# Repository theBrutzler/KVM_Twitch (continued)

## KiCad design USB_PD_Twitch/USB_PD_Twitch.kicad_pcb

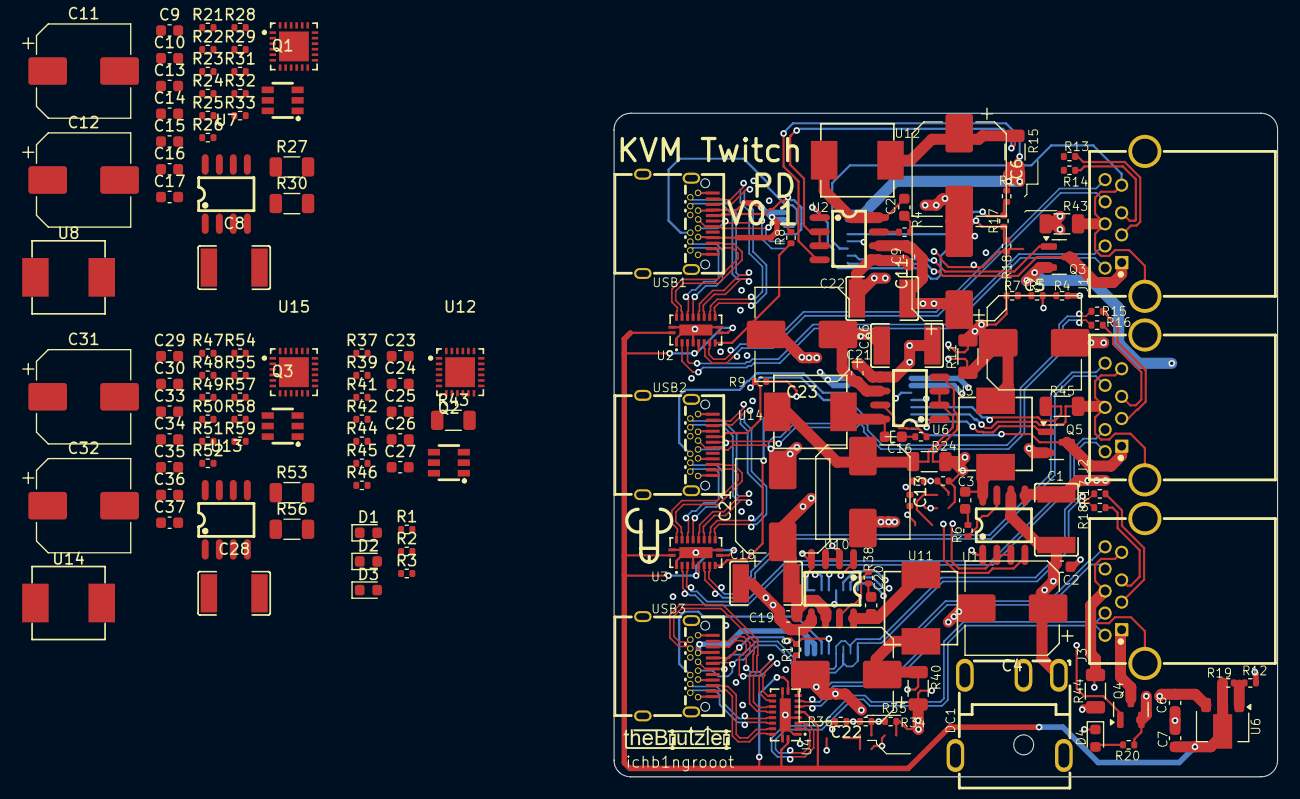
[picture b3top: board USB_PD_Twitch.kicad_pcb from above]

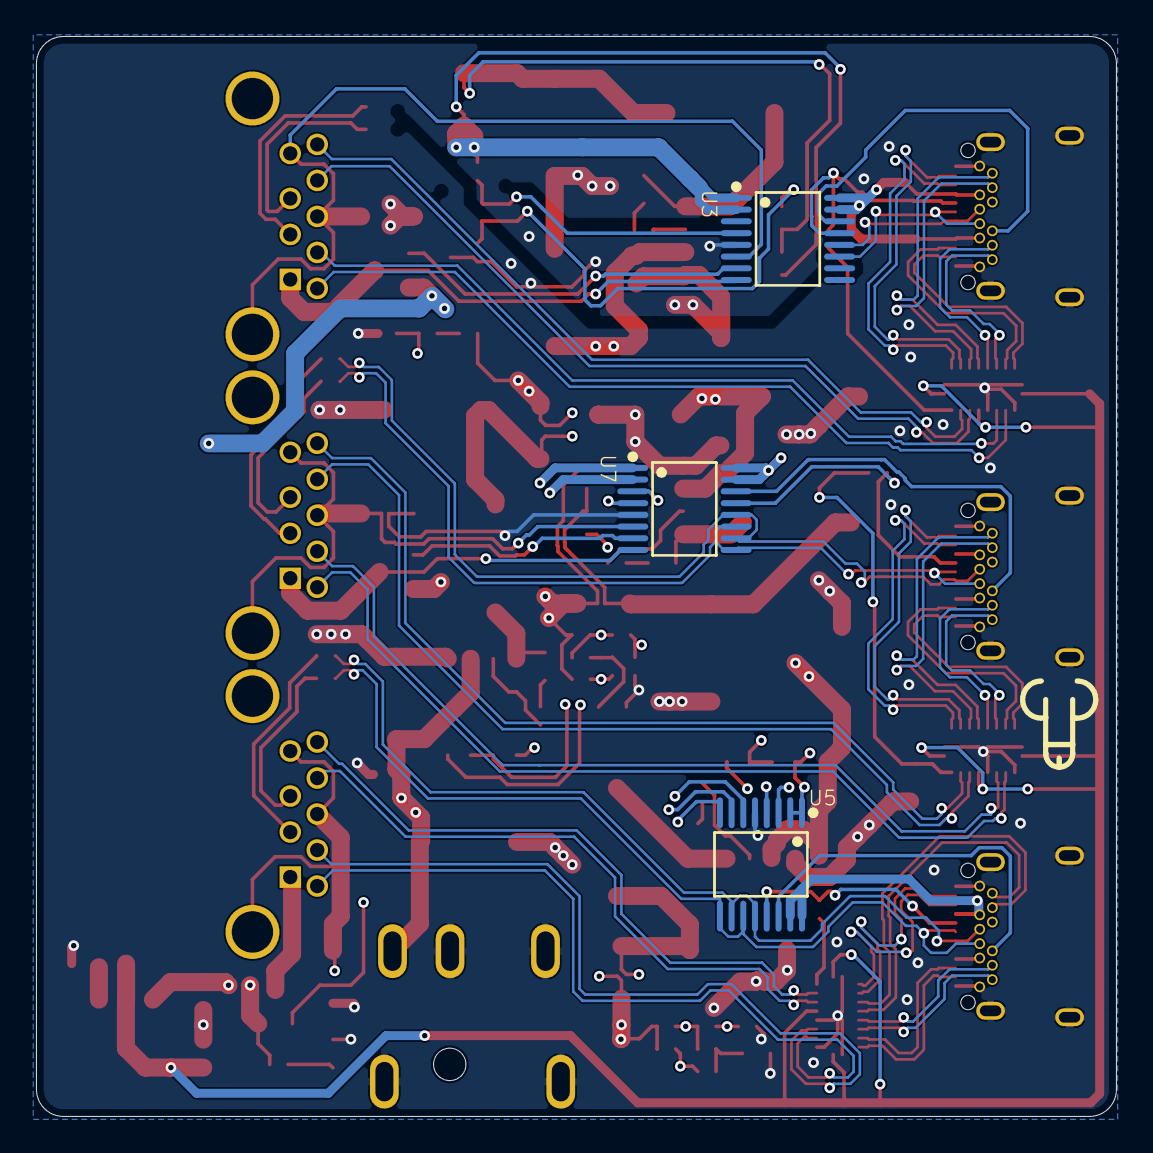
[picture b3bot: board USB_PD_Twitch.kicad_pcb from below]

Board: 4 copper layers, 60.0 x 60.0 mm, 158 parts (3 on the bottom side), 159 nets.

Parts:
C1: 2u2; C1812
C2, C2#2, C3, C9, C9#2, C10, C13#2, C14, C15, C16, C16#2, C17, C19, C20, C21#2, C23, C24, C25, C26#2, C27, C29, C30, C33, C34, C35, C36, C37: 100n; C_0603_1608Metric
C4, C5, C6#2, C11, C11#2, C12, C13, C21, C22#2, C23#2, C31, C32: 100u; CP_Elec_8x10
C6, C7: 10u; C_0603_1608Metric
C8, C18, C22, C26, C28: 22u; C1812
D1, D2, D3, D4: LED; LED_0603_1608Metric
DC1: DC-044A-25; DC-IN-TH_DC-044A-25A
J1, J2, J3: USB3_A; USB-3.0-A-TH_HC-ST-003-01-Z
Q1, Q2, Q3#2: FS8205A_C908265; SOT-23-6_L2.9-W1.6-P0.95-LS2.8-BR
Q3, Q4, Q5: Q_PMOS_GSD; SOT-23
R1, R2, R3, R12, R20, R28, R29, R41, R42, R54, R55: 10K; R_0402_1005Metric
R4, R6, R6#2, R13, R14, R15, R16, R17#2, R18#2, R25, R38, R51: 22R; R_0402_1005Metric
R4#2, R18, R23, R36, R37, R49: 25K; R_0402_1005Metric
R5, R17, R19, R22, R33, R35, R48: 8K; R_0402_1005Metric
R7, R16#2, R21, R31, R32#2, R33#2, R34, R44#2, R46, R47, R57, R59: 100K; R_0402_1005Metric
R8, R9, R10: 0R; R_0402_1005Metric
R11, R15#2, R24, R27, R40, R43#2, R44, R45, R53: 10m; R_1206_3216Metric
R24#2, R37#2, R50: 29K; R_0402_1005Metric
R26, R39, R52: 18K; R_0402_1005Metric
R30, R43, R56: 6m; R_1206_3216Metric
R32, R45#2, R58: 100R; R_0402_1005Metric
U1, U2#2, U6#2, U7, U10, U13: NDP1360KC; SOP-8_L4.9-W3.9-P1.27-LS6.0-BL
U2, U3, U4: CH482D; VFQFN-20_L4.5-W2.5-P0.5-BL-EP
U3#2, U5#2, U7#2: XPD738B20; TSSOP-16_L5.0-W4.4-P0.65-LS6.4-BL
U5, U8, U11, U12, U14, U14#2: CXP0650-220M-AG(22UH); IND-SMD_L7.1-W6.6_CXP0650
U6: LM317L_SOT-89; SOT-89-3
U9, U12#2, U15: TPS25740ARGER; VQFN-24_L4.0-W4.0-P0.50-TL-EP
USB1, USB2, USB3: HX TYPE-C 24P QCHT; TYPE-C-SMD_TYPE-C-24P-QCHT

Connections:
+3V3: C7.1, R1.1, R2.1, R3.1, R19.1, U2.5 (VDD), U2.9 (VDD), U2.20 (VDD), U3.5 (VDD), U3.9 (VDD), U3.20 (VDD), U4.5 (VDD), U4.9 (VDD), U4.20 (VDD), U6.2 (VO)
+5V: C6.1, J1.1 (VBUS), J2.1 (VBUS), J3.1 (VBUS), Q3.2 (S), Q4.2 (S), Q5.2 (S), R7.1, R11.2, R20.1, U1.4 (CSN2), U6.3 (VI)
+24V: C1.2, C2.2, C4.1, C8.2, C9.2, C9#2.2, C11.1, C11#2.1, C18.2, C19.2, C21.1, C21#2.2, C22.2, C23#2.1, C26.2, C28.2, C29.2, C31.1, DC1.4, U1.6 (VIN), U2#2.6 (VIN), U6#2.6 (VIN), U7.6 (VIN), U10.6 (VIN), U13.6 (VIN)
/A1_SSRX+: U2.14 (SSA1X), USB1.B11 (SSRXp1)
/A1_SSRX-: U2.13 (SSA1Y), USB1.B10 (SSRXn1)
/A1_SSTX+: U2.12 (SSB1X), USB1.A2 (SSTXp1)
/A1_SSTX-: U2.11 (SSB1Y), USB1.A3 (SSTXn1)
/A2_SSRX+: U2.18 (SSA0X), USB1.A11 (SSRXp2)
/A2_SSRX-: U2.17 (SSA0Y), USB1.A10 (SSRXn2)
/A2_SSTX+: U2.16 (SSB0X), USB1.B2 (SSTXp2)
/A2_SSTX-: U2.15 (SSB0Y), USB1.B3 (SSTXn2)
/A_CC1: R8.2, U3#2.13 (CC1), U9.2 (CC1), USB1.A5 (CC1)
/A_CC2: U3#2.14 (CC2), U9.3 (CC2), USB1.B5 (CC2)
/A_D+: R14.2, U3#2.11 (DP1), USB1.A6 (DP1), USB1.B6 (DP2)
/A_D-: R13.1, U3#2.12 (DM1), USB1.A7 (DN2), USB1.B7 (DN2)
/A_SSRX+: J1.6 (SSRX+), U2.6 (SSBX)
/A_SSRX-: J1.5 (SSRX-), U2.7 (SSBY)
/A_SSTX+: J1.9 (SSTX+), U2.2 (SSAX)
/A_SSTX-: J1.8 (SSTX-), U2.3 (SSAY)
/A_USB_CC_DET: D3.1 (K), U9.11 (~UFP)
/A_VBUS: R30.2, R32.1, U3#2.15 (VBUS), U3#2.16 (VBUS), U9.21 (VBUS), USB1.A4 (VBUS), USB1.A9 (VBUS), USB1.B4 (VBUS), USB1.B9 (VBUS)
/B1_SSRX+: U3.14 (SSA1X), USB2.B11 (SSRXp1)
/B1_SSRX-: U3.13 (SSA1Y), USB2.B10 (SSRXn1)
/B1_SSTX+: U3.12 (SSB1X), USB2.A2 (SSTXp1)
/B1_SSTX-: U3.11 (SSB1Y), USB2.A3 (SSTXn1)
/B2_SSRX+: U3.18 (SSA0X), USB2.A11 (SSRXp2)
/B2_SSRX-: U3.17 (SSA0Y), USB2.A10 (SSRXn2)
/B2_SSTX+: U3.16 (SSB0X), USB2.B2 (SSTXp2)
/B2_SSTX-: U3.15 (SSB0Y), USB2.B3 (SSTXn2)
/B_CC1: R9.2, U7#2.13 (CC1), U15.2 (CC1), USB2.A5 (CC1)
/B_CC2: U7#2.14 (CC2), U15.3 (CC2), USB2.B5 (CC2)
/B_D+: R16.2, U7#2.11 (DP1), USB2.A6 (DP1), USB2.B6 (DP2)
/B_D-: R15.1, U7#2.12 (DM1), USB2.A7 (DN2), USB2.B7 (DN2)
/B_SSRX+: J2.6 (SSRX+), U3.6 (SSBX)
/B_SSRX-: J2.5 (SSRX-), U3.7 (SSBY)
/B_SSTX+: J2.9 (SSTX+), U3.2 (SSAX)
/B_SSTX-: J2.8 (SSTX-), U3.3 (SSAY)
/B_USB_CC_DET: D1.1 (K), U15.11 (~UFP)
/B_VBUS: R56.2, R58.1, U7#2.15 (VBUS), U7#2.16 (VBUS), U15.21 (VBUS), USB2.A4 (VBUS), USB2.A9 (VBUS), USB2.B4 (VBUS), USB2.B9 (VBUS)
/C1_SSRX+: U4.14 (SSA1X), USB3.B11 (SSRXp1)
/C1_SSRX-: U4.13 (SSA1Y), USB3.B10 (SSRXn1)
/C1_SSTX+: U4.12 (SSB1X), USB3.A2 (SSTXp1)
/C1_SSTX-: U4.11 (SSB1Y), USB3.A3 (SSTXn1)
/C2_SSRX+: U4.18 (SSA0X), USB3.A11 (SSRXp2)
/C2_SSRX-: U4.17 (SSA0Y), USB3.A10 (SSRXn2)
/C2_SSTX+: U4.16 (SSB0X), USB3.B2 (SSTXp2)
/C2_SSTX-: U4.15 (SSB0Y), USB3.B3 (SSTXn2)
/C_CC1: R10.2, U5#2.13 (CC1), U12#2.2 (CC1), USB3.A5 (CC1)
/C_CC2: U5#2.14 (CC2), U12#2.3 (CC2), USB3.B5 (CC2)
/C_D+: R18#2.2, U5#2.11 (DP1), USB3.A6 (DP1), USB3.B6 (DP2)
/C_D-: R17#2.1, U5#2.12 (DM1), USB3.A7 (DN2), USB3.B7 (DN2)
/C_SSRX+: J3.6 (SSRX+), U4.6 (SSBX)
/C_SSRX-: J3.5 (SSRX-), U4.7 (SSBY)
/C_SSTX+: J3.9 (SSTX+), U4.2 (SSAX)
/C_SSTX-: J3.8 (SSTX-), U4.3 (SSAY)
/C_USB_CC_DET: D2.1 (K), U12#2.11 (~UFP)
/C_VBUS: R43.2, R45#2.1, U5#2.15 (VBUS), U5#2.16 (VBUS), U12#2.21 (VBUS), USB3.A4 (VBUS), USB3.A9 (VBUS), USB3.B4 (VBUS), USB3.B9 (VBUS)
/USB_PD1/CTL1: R26.2, U9.6 (CTL1)
/USB_PD1/CTL2: R24#2.2, U9.7 (CTL2)
/USB_PD1/USB2_GND: R45.2, U7#2.6 (ISP2)
/USB_PD1/USB2_VBUS: Q5.3 (D), U7#2.8 (VBUSA)
/USB_PD2/CTL1: R52.2, U15.6 (CTL1)
/USB_PD2/CTL2: R50.2, U15.7 (CTL2)
/USB_PD2/USB2_GND: R44.2, U5#2.6 (ISP2)
/USB_PD2/USB2_VBUS: Q4.3 (D), U5#2.8 (VBUSA)
/USB_PD3/CTL1: R39.2, U12#2.6 (CTL1)
/USB_PD3/CTL2: R37#2.2, U12#2.7 (CTL2)
/USB_PD/USB2_GND: R43#2.2, U3#2.6 (ISP2)
/USB_PD/USB2_VBUS: Q3.3 (D), U3#2.8 (VBUSA)
GND: C1.1, C2.1, C4.2, C5.2, C6.2, C6#2.2, C7.2, C8.1, C9.1, C9#2.1, C11.2, C11#2.2, C12.2, C13.2, C13#2.2, C14.2, C15.2, C16#2.2, C17.2, C18.1, C19.1, C21.2, C21#2.1, C22.1, C22#2.2, C23.2, C23#2.2, C24.2, C25.2, C26.1, C26#2.2, C27.2, C28.1, C29.1, C31.2, C32.2, C33.2, C34.2, C35.2, C36.2, C37.2, D4.1 (K), DC1.1, DC1.2, DC1.3, DC1.5, J1.4 (GND), J1.7 (DRAIN), J1.10 (SHIELD), J2.4 (GND), J2.7 (DRAIN), J2.10 (SHIELD), J3.4 (GND), J3.7 (DRAIN), J3.10 (SHIELD), R4#2.2, R12.2, R18.2, R23.2, R33#2.1, R36.2, R37.2, R43#2.1, R44.1, R45.1, R46.1, R49.2, R59.1, U1.5 (GND), U2.1 (~EN), U2.4 (GND), U2.10 (GND), U2.19 (GND), U2.21 (GND), U2#2.5 (GND), U3.1 (~EN), U3.4 (GND), U3.10 (GND), U3.19 (GND), U3.21 (GND), U3#2.5 (GND), U4.1 (~EN), U4.4 (GND), U4.10 (GND), U4.19 (GND), U4.21 (GND), U5#2.5 (GND), U6#2.5 (GND), U7.5 (GND), U7#2.5 (GND), U9.4 (GND), U9.5 (HIPWR), U9.8 (~EN12V/~EN9V), U9.17 (VDD), U9.18 (AGND), U9.25 (EP), U10.5 (GND), U12#2.4 (GND), U12#2.5 (HIPWR), U12#2.8 (~EN12V/~EN9V), U12#2.17 (VDD), U12#2.18 (AGND), U12#2.25 (EP), U13.5 (GND), U15.4 (GND), U15.5 (HIPWR), U15.8 (~EN12V/~EN9V), U15.17 (VDD), U15.18 (AGND), U15.25 (EP), USB1.25, USB1.A1 (GND), USB1.A12 (GND), USB1.B1 (GND), USB1.B12 (GND), USB2.25, USB2.A1 (GND), USB2.A12 (GND), USB2.B1 (GND), USB2.B12 (GND), USB3.25, USB3.A1 (GND), USB3.A12 (GND), USB3.B1 (GND), USB3.B12 (GND)
unnamed: C2#2.1, R4.2
unnamed: C3.1, R6.2
unnamed: C10.1, R25.2
unnamed: C13#2.1, R29.2
unnamed: C16.1, R6#2.2
unnamed: C20.1, R38.2
unnamed: C23.1, R42.2
unnamed: C30.1, R51.2
unnamed: C33.1, R55.2
unnamed: D1.2 (A), R1.2
unnamed: D2.2 (A), R2.2
unnamed: D3.2 (A), R3.2
unnamed: D4.2 (A), R20.2
unnamed: J1.3 (D+), R14.1
unnamed: J1.2 (D-), R13.2
unnamed: J2.3 (D+), R16.1
unnamed: J2.2 (D-), R15.2
unnamed: J3.3 (D+), R18#2.1
unnamed: J3.2 (D-), R17#2.2
unnamed: Q1.4 (G2), Q1.6 (G1), R28.1
unnamed: Q1.1 (S1), Q1.3 (S2), R30.1, U9.19 (ISNS), U9.23 (GDNS)
unnamed: Q2.4 (G2), Q2.6 (G1), R41.1
unnamed: Q2.1 (S1), Q2.3 (S2), R43.1, U12#2.19 (ISNS), U12#2.23 (GDNS)
unnamed: Q3#2.4 (G2), Q3#2.6 (G1), R54.1
unnamed: Q3.1 (G), U3#2.7 (GD2)
unnamed: Q3#2.1 (S1), Q3#2.3 (S2), R56.1, U15.19 (ISNS), U15.23 (GDNS)
unnamed: Q4.1 (G), U5#2.7 (GD2)
unnamed: Q5.1 (G), U7#2.7 (GD2)
unnamed: R5.2, R7.2
unnamed: R21.2, R22.2
unnamed: R34.2, R35.2
unnamed: R47.2, R48.2
unnamed: R6.1, U1.7 (BST)
unnamed: C5.1, R11.1, U1.2 (CSP), U1.3 (CSN1), U5.2
unnamed: R4#2.1, R5.1, U1.1 (FB)
unnamed: C3.2, U1.8 (SW), U5.1
unnamed: R4.1, U2#2.7 (BST)
unnamed: C6#2.1, R15#2.1, U2#2.2 (CSP), U2#2.3 (CSN1), U12.2
unnamed: R15#2.2, R16#2.1, U2#2.4 (CSN2), U3#2.1 (VPWR), U3#2.2 (VPWR)
unnamed: R17.1, R18.1, U2#2.1 (FB)
unnamed: R8.1, U2.8 (SEL)
unnamed: C2#2.2, U2#2.8 (SW), U12.1
unnamed: R9.1, U3.8 (SEL)
unnamed: R16#2.2, R17.2, U3#2.4 (VFB)
unnamed: U5#2.1 (VPWR), U5#2.2 (VPWR)
unnamed: R10.1, U4.8 (SEL)
unnamed: R12.1, R19.2, U6.1 (ADJ)
unnamed: R6#2.1, U6#2.7 (BST)
unnamed: C13.1, R24.1, U6#2.2 (CSP), U6#2.3 (CSN1), U14.2
unnamed: R24.2, R32#2.1, U6#2.4 (CSN2), U7#2.1 (VPWR), U7#2.2 (VPWR)
unnamed: R33.1, R37.1, U6#2.1 (FB)
unnamed: C16.2, U6#2.8 (SW), U14.1
unnamed: R25.1, U7.7 (BST)
unnamed: C12.1, R27.1, U7.2 (CSP), U7.3 (CSN1), U8.2
unnamed: Q1.2 (D1/D2), Q1.5 (D1/D2), R21.1, R27.2, U7.4 (CSN2), U9.20 (VPWR)
unnamed: R22.1, R23.1, R24#2.1, R26.1, U7.1 (FB)
unnamed: C10.2, U7.8 (SW), U8.1
unnamed: R32#2.2, R33.2, U7#2.4 (VFB)
unnamed: R32.2, U9.24 (DSCG)
unnamed: C15.1, C16#2.1, U9.13 (DVDD), U9.15 (~GD)
unnamed: R28.2, R29.1, U9.22 (GDNG)
unnamed: R31.2, U9.14 (PCTRL)
unnamed: R33#2.2, U9.12 (PSEL)
unnamed: C14.1, R31.1, U9.16 (VAUX)
unnamed: C17.1, U9.1 (VTX)
unnamed: R38.1, U10.7 (BST)
unnamed: C22#2.1, R40.1, U10.2 (CSP), U10.3 (CSN1), U11.2
unnamed: Q2.2 (D1/D2), Q2.5 (D1/D2), R34.1, R40.2, U10.4 (CSN2), U12#2.20 (VPWR)
unnamed: R35.1, R36.1, R37#2.1, R39.1, U10.1 (FB)
unnamed: C20.2, U10.8 (SW), U11.1
unnamed: R45#2.2, U12#2.24 (DSCG)
unnamed: C25.1, C26#2.1, U12#2.13 (DVDD), U12#2.15 (~GD)
unnamed: R41.2, R42.1, U12#2.22 (GDNG)
unnamed: R44#2.2, U12#2.14 (PCTRL)
unnamed: R46.2, U12#2.12 (PSEL)
unnamed: C24.1, R44#2.1, U12#2.16 (VAUX)
unnamed: C27.1, U12#2.1 (VTX)
unnamed: R51.1, U13.7 (BST)
unnamed: C32.1, R53.1, U13.2 (CSP), U13.3 (CSN1), U14#2.2
unnamed: Q3#2.2 (D1/D2), Q3#2.5 (D1/D2), R47.1, R53.2, U13.4 (CSN2), U15.20 (VPWR)
unnamed: R48.1, R49.1, R50.1, R52.1, U13.1 (FB)
unnamed: C30.2, U13.8 (SW), U14#2.1
unnamed: R58.2, U15.24 (DSCG)
unnamed: C35.1, C36.1, U15.13 (DVDD), U15.15 (~GD)
unnamed: R54.2, R55.1, U15.22 (GDNG)
unnamed: R57.2, U15.14 (PCTRL)
unnamed: R59.2, U15.12 (PSEL)
unnamed: C34.1, R57.1, U15.16 (VAUX)
unnamed: C37.1, U15.1 (VTX)

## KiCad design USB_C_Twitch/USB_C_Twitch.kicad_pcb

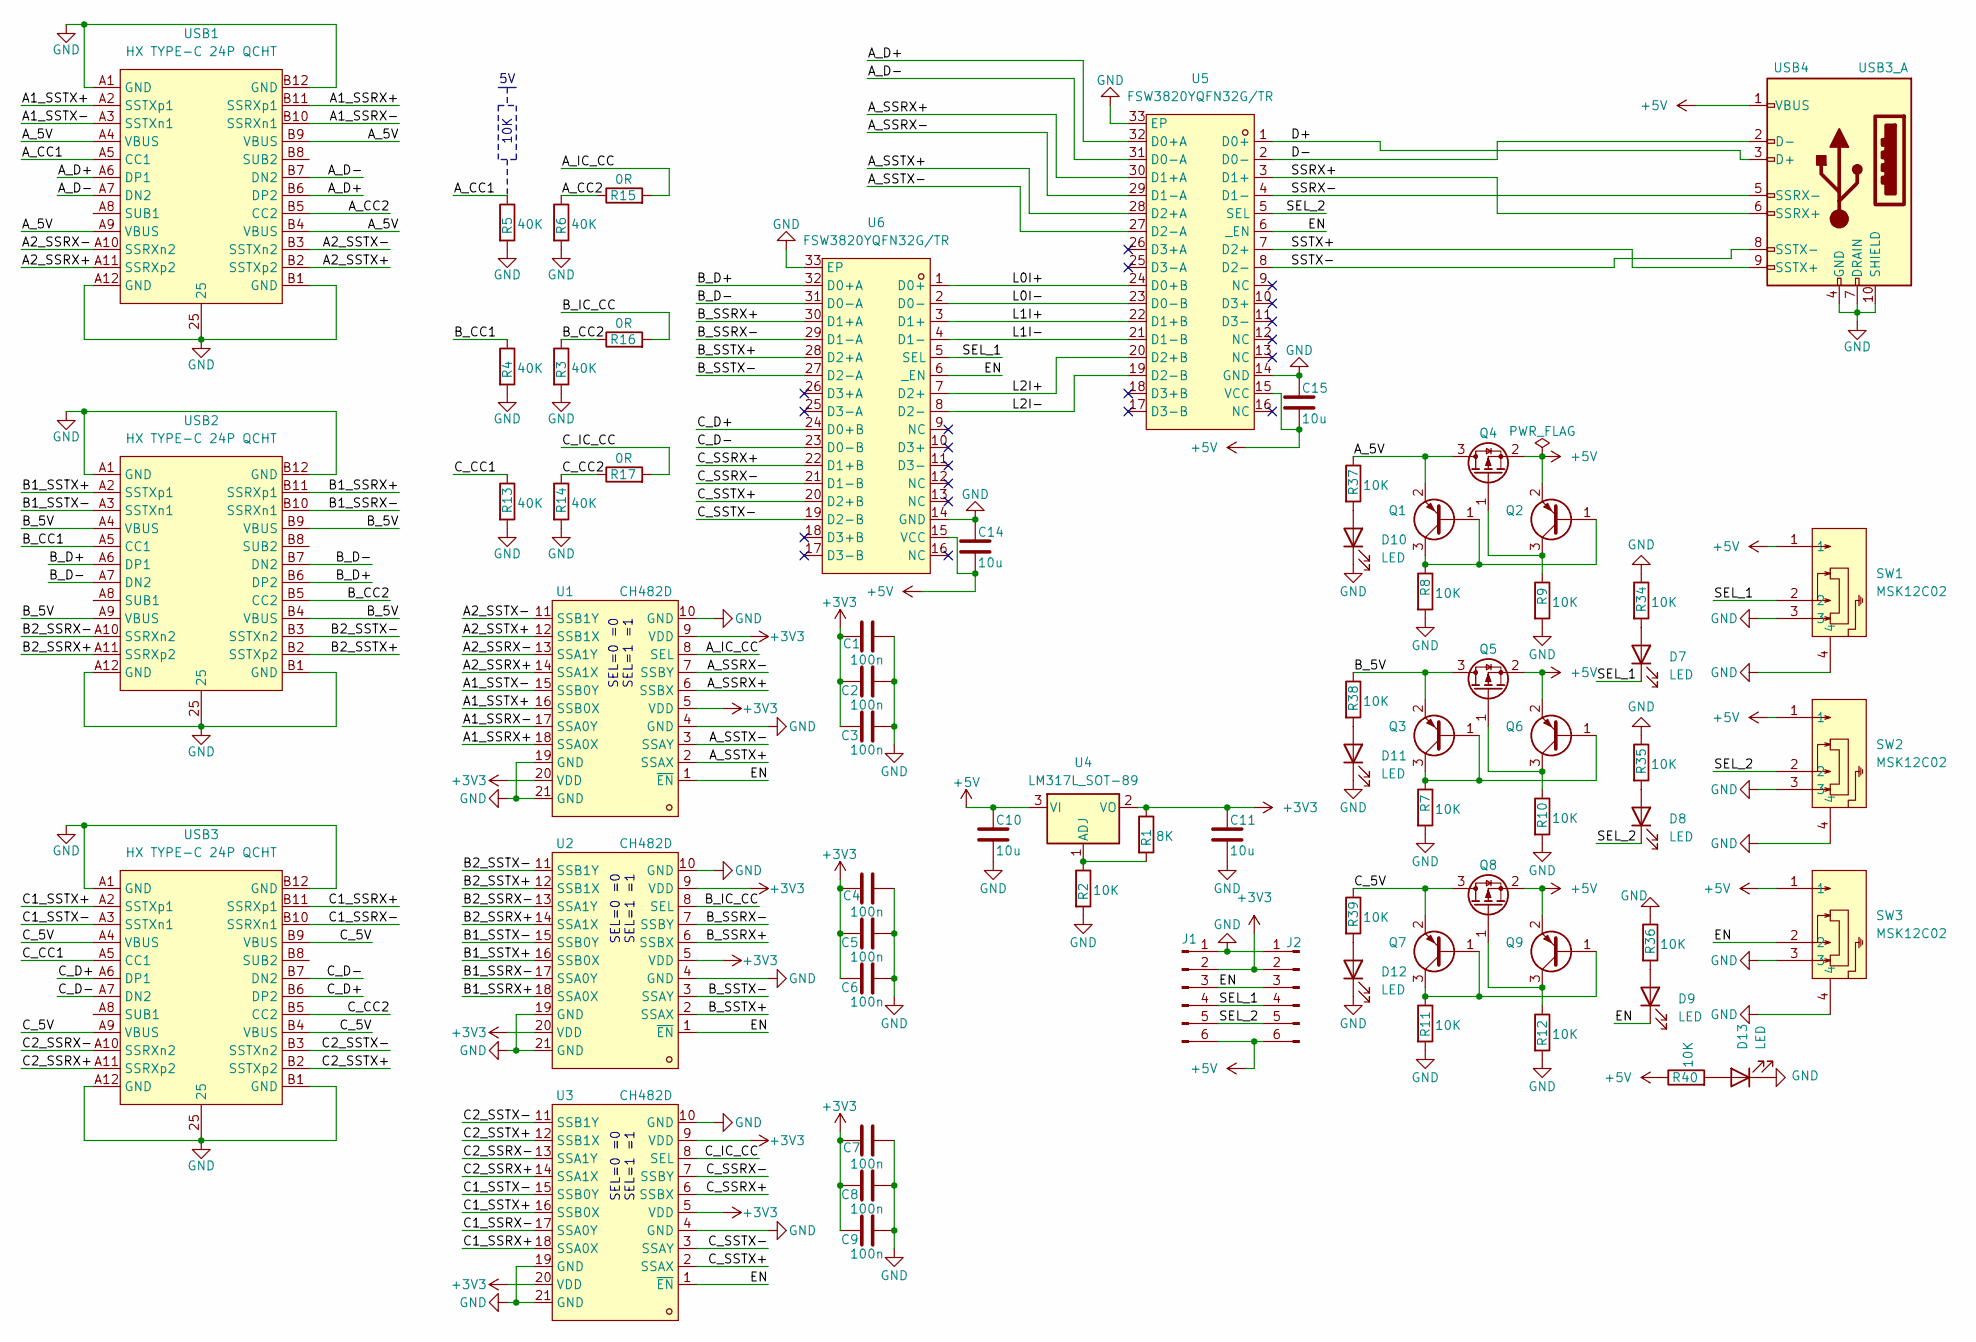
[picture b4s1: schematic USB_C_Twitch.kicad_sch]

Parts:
C1, C2, C3, C4, C5, C6, C7, C8, C9: 100n; C_0603_1608Metric; LCSC C344189
C10, C11, C14, C15: 10u; C_0603_1608Metric; LCSC C6119842
D7, D8, D9, D10, D11, D12, D13: LED; LED_0603_1608Metric; LCSC C7496819
J1, J2: Conn_01x06_Pin; JST_XH_B6B-XH-AM_1x06_P2.50mm_Vertical; LCSC C144397
Q1, Q2, Q3, Q6, Q7, Q9: Q_PNP_BEC; SOT-23-3_L2.9-W1.3-P1.90-LS2.4-BR; LCSC C2891805
Q4, Q5, Q8: Q_PMOS_GSD; SOT-23; LCSC C41384537
R1: 8K; R_0402_1005Metric; LCSC C2960789
R2, R7, R8, R9, R10, R11, R12, R34, R35, R36, R37, R38, R39, R40: 10K; R_0402_1005Metric; LCSC C102759
R3, R4, R5, R6, R13, R14: 40K; R_0402_1005Metric; LCSC C102759
R15, R16, R17: 0R; R_0402_1005Metric
SW1, SW2, SW3: MSK12C02; SW-TH_MSK12C02; LCSC Part C431540
U1, U2, U3: CH482D; VFQFN-20_L4.5-W2.5-P0.5-BL-EP; LCSC Part C2913009
U4: LM317L_SOT-89; SOT-89-3; LCSC C45953613
U5, U6: FSW3820YQFN32G/TR; QFN-32_L4.0-W4.0-P0.40-TL-EP2.9; LCSC Part C32713321
USB1, USB2, USB3: HX TYPE-C 24P QCHT; TYPE-C-SMD_TYPE-C-24P-QCHT; LCSC Part C5178545
USB4: USB3_A; USB-3.0-A-TH_HC-ST-003-01-Z; LCSC Part C2845330

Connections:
+3V3: C1.2, C2.2, C3.2, C4.2, C5.2, C6.2, C7.2, C8.2, C9.2, C11.1, J1.2, J2.2, R1.1, U1.5 (VDD), U1.9 (VDD), U1.20 (VDD), U2.5 (VDD), U2.9 (VDD), U2.20 (VDD), U3.5 (VDD), U3.9 (VDD), U3.20 (VDD), U4.2 (VO)
+5V: C10.1, C14.2, C15.2, J1.6, J2.6, Q2.2 (E), Q4.2 (S), Q5.2 (S), Q6.2 (E), Q8.2 (S), Q9.2 (E), R40.1, SW1.1, SW2.1, SW3.1, U4.3 (VI), U5.15 (VCC), U6.15 (VCC), USB4.1 (VBUS)
/A1_SSRX+: U1.18 (SSA0X), USB1.B11 (SSRXp1)
/A1_SSRX-: U1.17 (SSA0Y), USB1.B10 (SSRXn1)
/A1_SSTX+: U1.16 (SSB0X), USB1.A2 (SSTXp1)
/A1_SSTX-: U1.15 (SSB0Y), USB1.A3 (SSTXn1)
/A2_SSRX+: U1.14 (SSA1X), USB1.A11 (SSRXp2)
/A2_SSRX-: U1.13 (SSA1Y), USB1.A10 (SSRXn2)
/A2_SSTX+: U1.12 (SSB1X), USB1.B2 (SSTXp2)
/A2_SSTX-: U1.11 (SSB1Y), USB1.B3 (SSTXn2)
/A_5V: Q1.2 (E), Q4.3 (D), R37.1, USB1.A4 (VBUS), USB1.A9 (VBUS), USB1.B4 (VBUS), USB1.B9 (VBUS)
/A_CC1: R5.1, USB1.A5 (CC1)
/A_CC2: R6.1, R15.1, USB1.B5 (CC2)
/A_D+: U5.32 (D0+A), USB1.A6 (DP1), USB1.B6 (DP2)
/A_D-: U5.31 (D0-A), USB1.A7 (DN2), USB1.B7 (DN2)
/A_IC_CC: R15.2, U1.8 (SEL)
/A_SSRX+: U1.6 (SSBX), U5.30 (D1+A)
/A_SSRX-: U1.7 (SSBY), U5.29 (D1-A)
/A_SSTX+: U1.2 (SSAX), U5.28 (D2+A)
/A_SSTX-: U1.3 (SSAY), U5.27 (D2-A)
/B1_SSRX+: U2.18 (SSA0X), USB2.B11 (SSRXp1)
/B1_SSRX-: U2.17 (SSA0Y), USB2.B10 (SSRXn1)
/B1_SSTX+: U2.16 (SSB0X), USB2.A2 (SSTXp1)
/B1_SSTX-: U2.15 (SSB0Y), USB2.A3 (SSTXn1)
/B2_SSRX+: U2.14 (SSA1X), USB2.A11 (SSRXp2)
/B2_SSRX-: U2.13 (SSA1Y), USB2.A10 (SSRXn2)
/B2_SSTX+: U2.12 (SSB1X), USB2.B2 (SSTXp2)
/B2_SSTX-: U2.11 (SSB1Y), USB2.B3 (SSTXn2)
/B_5V: Q3.2 (E), Q5.3 (D), R38.1, USB2.A4 (VBUS), USB2.A9 (VBUS), USB2.B4 (VBUS), USB2.B9 (VBUS)
/B_CC1: R4.1, USB2.A5 (CC1)
/B_CC2: R3.1, R16.1, USB2.B5 (CC2)
/B_D+: U6.32 (D0+A), USB2.A6 (DP1), USB2.B6 (DP2)
/B_D-: U6.31 (D0-A), USB2.A7 (DN2), USB2.B7 (DN2)
/B_IC_CC: R16.2, U2.8 (SEL)
/B_SSRX+: U2.6 (SSBX), U6.30 (D1+A)
/B_SSRX-: U2.7 (SSBY), U6.29 (D1-A)
/B_SSTX+: U2.2 (SSAX), U6.28 (D2+A)
/B_SSTX-: U2.3 (SSAY), U6.27 (D2-A)
/C1_SSRX+: U3.18 (SSA0X), USB3.B11 (SSRXp1)
/C1_SSRX-: U3.17 (SSA0Y), USB3.B10 (SSRXn1)
/C1_SSTX+: U3.16 (SSB0X), USB3.A2 (SSTXp1)
/C1_SSTX-: U3.15 (SSB0Y), USB3.A3 (SSTXn1)
/C2_SSRX+: U3.14 (SSA1X), USB3.A11 (SSRXp2)
/C2_SSRX-: U3.13 (SSA1Y), USB3.A10 (SSRXn2)
/C2_SSTX+: U3.12 (SSB1X), USB3.B2 (SSTXp2)
/C2_SSTX-: U3.11 (SSB1Y), USB3.B3 (SSTXn2)
/C_5V: Q7.2 (E), Q8.3 (D), R39.1, USB3.A4 (VBUS), USB3.A9 (VBUS), USB3.B4 (VBUS), USB3.B9 (VBUS)
/C_CC1: R13.1, USB3.A5 (CC1)
/C_CC2: R14.1, R17.1, USB3.B5 (CC2)
/C_D+: U6.24 (D0+B), USB3.A6 (DP1), USB3.B6 (DP2)
/C_D-: U6.23 (D0-B), USB3.A7 (DN2), USB3.B7 (DN2)
/C_IC_CC: R17.2, U3.8 (SEL)
/C_SSRX+: U3.6 (SSBX), U6.22 (D1+B)
/C_SSRX-: U3.7 (SSBY), U6.21 (D1-B)
/C_SSTX+: U3.2 (SSAX), U6.20 (D2+B)
/C_SSTX-: U3.3 (SSAY), U6.19 (D2-B)
/D+: U5.1 (D0+), USB4.3 (D+)
/D-: U5.2 (D0-), USB4.2 (D-)
/EN: D9.1 (K), J1.3, J2.3, SW3.2, U1.1 (~EN), U2.1 (~EN), U3.1 (~EN), U5.6 (_EN), U6.6 (_EN)
/L0I+: U5.24 (D0+B), U6.1 (D0+)
/L0I-: U5.23 (D0-B), U6.2 (D0-)
/L1I+: U5.22 (D1+B), U6.3 (D1+)
/L1I-: U5.21 (D1-B), U6.4 (D1-)
/L2I+: U5.20 (D2+B), U6.7 (D2+)
/L2I-: U5.19 (D2-B), U6.8 (D2-)
/SEL_1: D7.1 (K), J1.4, J2.4, SW1.2, U6.5 (SEL)
/SEL_2: D8.1 (K), J1.5, J2.5, SW2.2, U5.5 (SEL)
/SSRX+: U5.3 (D1+), USB4.6 (SSRX+)
/SSRX-: U5.4 (D1-), USB4.5 (SSRX-)
/SSTX+: U5.7 (D2+), USB4.9 (SSTX+)
/SSTX-: U5.8 (D2-), USB4.8 (SSTX-)
GND: C1.1, C2.1, C3.1, C4.1, C5.1, C6.1, C7.1, C8.1, C9.1, C10.2, C11.2, C14.1, C15.1, D10.1 (K), D11.1 (K), D12.1 (K), D13.1 (K), J1.1, J2.1, R2.2, R3.2, R4.2, R5.2, R6.2, R7.2, R8.2, R9.2, R10.2, R11.2, R12.2, R13.2, R14.2, R34.1, R35.1, R36.1, SW1.3, SW1.4, SW2.3, SW2.4, SW3.3, SW3.4, U1.4 (GND), U1.10 (GND), U1.19 (GND), U1.21 (GND), U2.4 (GND), U2.10 (GND), U2.19 (GND), U2.21 (GND), U3.4 (GND), U3.10 (GND), U3.19 (GND), U3.21 (GND), U5.14 (GND), U5.33 (EP), U6.14 (GND), U6.33 (EP), USB1.25, USB1.A1 (GND), USB1.A12 (GND), USB1.B1 (GND), USB1.B12 (GND), USB2.25, USB2.A1 (GND), USB2.A12 (GND), USB2.B1 (GND), USB2.B12 (GND), USB3.25, USB3.A1 (GND), USB3.A12 (GND), USB3.B1 (GND), USB3.B12 (GND), USB4.4 (GND), USB4.7 (DRAIN), USB4.10 (SHIELD)
unnamed: D7.2 (A), R34.2
unnamed: D8.2 (A), R35.2
unnamed: D9.2 (A), R36.2
unnamed: D10.2 (A), R37.2
unnamed: D11.2 (A), R38.2
unnamed: D12.2 (A), R39.2
unnamed: D13.2 (A), R40.2
unnamed: Q1.1 (B), Q1.3 (C), Q2.1 (B), R8.1
unnamed: Q2.3 (C), Q4.1 (G), R9.1
unnamed: Q3.1 (B), Q3.3 (C), Q6.1 (B), R7.1
unnamed: Q5.1 (G), Q6.3 (C), R10.1
unnamed: Q7.1 (B), Q7.3 (C), Q9.1 (B), R11.1
unnamed: Q8.1 (G), Q9.3 (C), R12.1
unnamed: R1.2, R2.1, U4.1 (ADJ)

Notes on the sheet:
SEL=0 =0 SEL=1 =1
10K

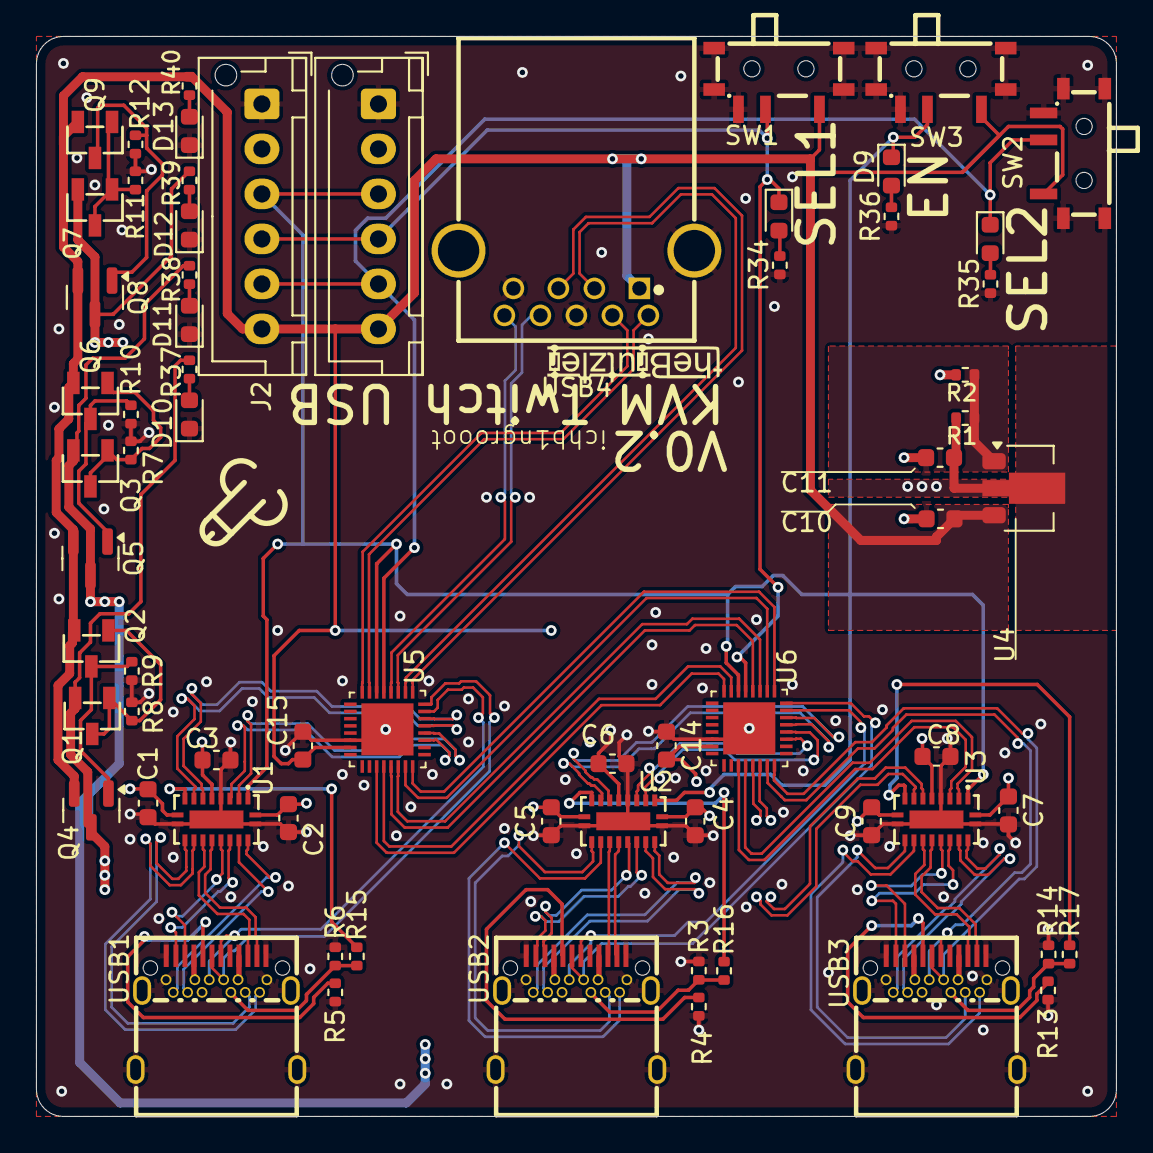
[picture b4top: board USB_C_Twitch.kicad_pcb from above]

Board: 4 copper layers, 60.0 x 60.0 mm, 68 parts (0 on the bottom side), 86 nets.

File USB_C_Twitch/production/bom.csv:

Designator,Footprint,Quantity,Value,LCSC Part #
"C1, C2, C3, C4, C5, C6, C7, C8, C9",0603,9,100n,
"C10, C11, C14, C15",0603,4,10u,
"D10, D11, D12, D13, D7, D8, D9",0603,7,LED,
"J1, J2",JST_XH_B6B-XH-AM_1x06_P2.50mm_Vertical,2,Conn_01x06_Pin,
"Q1, Q2, Q3, Q6, Q7, Q9",SOT-23-3_L2.9-W1.3-P1.90-LS2.4-BR,6,Q_PNP_BEC,C2891805
"Q4, Q5, Q8",SOT-23,3,Q_PMOS_GSD,C41384537
R1,0402,1,8K,
"R10, R11, R12, R13, R14, R2, R3, R34, R35, R36, R37, R38, R39, R4, R40, R5, R6, R7, R8, R9",0402,20,10K,
"R15, R16, R17",0402,3,0R,
"SW1, SW2, SW3",SW-TH_MSK12C02,3,MSK12C02,C431540
"U1, U2, U3",VFQFN-20_L4.5-W2.5-P0.5-BL-EP,3,CH482D,C2913009
U4,SOT-89-3,1,LM317L_SOT-89,
"U5, U6",QFN-32_L4.0-W4.0-P0.40-TL-EP2.9,2,FSW3820YQFN32G/TR,C32713321
"USB1, USB2, USB3",TYPE-C-SMD_TYPE-C-24P-QCHT,3,HX TYPE-C 24P QCHT,C5178545
USB4,USB-3.0-A-TH_HC-ST-003-01-Z,1,USB3_A,C2845330

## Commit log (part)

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2025-08-28 Initial Upload
2025-08-28 Add Pictures
2025-08-28 add readme file
2026-06-23 add nev versions. (usb c and displayport working)
